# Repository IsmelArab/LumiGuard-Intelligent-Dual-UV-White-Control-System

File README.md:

# LumiGuard-Intelligent-Dual-UV-White-Control-System

# Project Objective:

LumiGuard's goal is to provide a comprehensive solution for applications that require:

Efficient UV disinfection: Using short-wavelength ultraviolet light (275 nm) to eliminate pathogens without risk to operators.

Adjustable white lighting: For real-time process visualization.

Smart security: Proximity detection automatically deactivates UV light if an operator approaches.

Energy efficiency: PWM control of LEDs and low-power mode.

# Key Components and Technologies:

The heart of LumiGuard integrates modern technologies and high-quality components:

ATtiny85 Microcontroller:

The brain of the system manages operating modes, PWM signals, and I2C communication.

VCNL4040 Proximity Sensor:

Detects human presence up to 20 cm away, activating safety protocols.

Specialized LEDs:

UV (275 nm): For disinfection.

White (5630 SMD): For cool, adjustable lighting.

MOSFET Control (DMN3010LSS):

Adjusts light intensity via PWM, minimizing energy losses

Professional PCB Design:

2 layers with a solid ground plane.

Noise filtering, analog/digital separation, and custom silkscreen printing.

Programming Interface (USBasp):

ISP connector for firmware updates.

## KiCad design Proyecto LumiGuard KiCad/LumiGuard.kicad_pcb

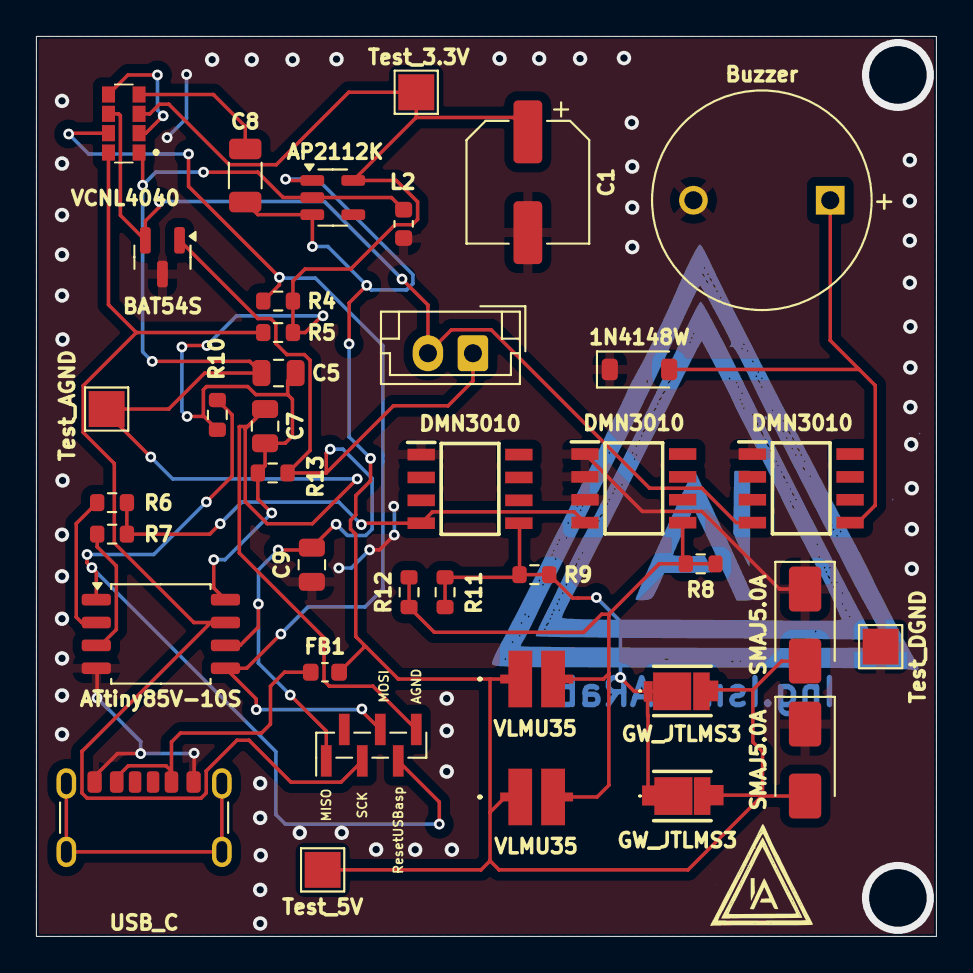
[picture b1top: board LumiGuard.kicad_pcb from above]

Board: 2 copper layers, 50.0 x 50.0 mm, 39 parts (0 on the bottom side), 18 nets.

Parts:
BZ1: Buzzer; MagneticBuzzer_ProSignal_ABI-009-RC
C1: 100uF; CP_Elec_6.3x5.3
C5: 1uF; C_0805_2012Metric
C7, C9: 0.1uF; C_0805_2012Metric
C8: 2.2uF; C_1206_3216Metric
D1: 1N4148W; D_SOD-123
D2: BAT54S; SOT-23
D5, D6: SMAJ5.0A; D_SMA
FB1: 2A; L_0603_1608Metric
IC1: VCNL4040; VCNL4040M3OEH3
J1: Conn_01x02_Pin; JST_EH_B2B-EH-A_1x02_P2.50mm_Vertical
J2: USB_C; USB_C_Receptacle_GCT_USB4125-xx-x-0190_6P_TopMnt_Horizontal
L2: 100uH; L_0603_1608Metric
LED2, LED4: GW_JTLMS3; GWJTLMS3CMG6G9XX5101
LED3, LED6: VLMU35; VLMU35CL20275120
Q1, Q2, Q3: DMN3010; SOIC127P600X175-8N
R4, R5: 2.2k; R_0603_1608Metric
R6, R7, R8, R12: 100; R_0603_1608Metric
R9, R11: 150; R_0603_1608Metric
R10, R13: 10k; R_0603_1608Metric
SPI1: TSW-106-08-F-S; PinHeader_1x06_P1.00mm_Vertical_SMD_Pin1Left
TP1: Test_5V; TestPoint_Pad_2.0x2.0mm
TP2: Test_3.3V; TestPoint_Pad_2.0x2.0mm
TP3: Test_DGND; TestPoint_Pad_2.0x2.0mm
TP4: Test_AGND; TestPoint_Pad_2.0x2.0mm
U1: AP2112K; SOT-23-5
U3: ATtiny85V-10S; SOIC-8_5.3x5.3mm_P1.27mm

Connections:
/Uc: Q1.4 (G), Q2.4 (G), R6.1, R7.1
AGND: C5.1, C7.1, IC1.1 (GND), L2.1, SPI1.6, TP4.1, U1.2 (GND)
Buzzer: BZ1.1 (+), D1.2 (A), Q3.5 (D_1)
DGND: BZ1.2 (-), C1.2, C9.1, D1.1 (K), D2.3 (COM), D5.1 (A1), D6.1 (A1), J2.A12 (GND), J2.B12 (GND), L2.2, Q1.1 (S_1), Q2.1 (S_1), Q2.2 (S_2), Q2.3 (S_3), Q3.1 (S_1), TP3.1, U3.4 (GND)
DLedB: LED2.1 (K_1), LED2.3 (K_2), LED4.1 (K_1), LED4.3 (K_2), Q1.5 (D_1), R9.1, R9.2, R11.1, R11.2
DLedUV: LED3.2 (K_1), LED3.4 (K_2), LED6.2 (K_1), LED6.4 (K_2), Q2.5 (D_1), R8.1, R8.2, R12.1, R12.2
INT/GMofetBuzzer: D2.2 (K), IC1.6 (INT), J1.2, Q3.4 (G)
unnamed: C8.1, IC1.4 (ANODE)
unnamed: IC1.2 (CATHODE_(SENSOR)), IC1.5 (CATHODE_(LED))
PW3.3V: C1.1, C5.2, C7.2, IC1.3 (VDD), R4.2, R5.2, R10.2, R13.2, TP2.1, U1.5 (VOUT), U3.8 (VCC)
PW5V: C8.2, D5.2 (A2), D6.2 (A2), FB1.2, LED2.2 (A_1), LED2.4 (A_2), LED3.1 (A_1), LED3.3 (A_2), LED4.2 (A_1), LED4.4 (A_2), LED6.1 (A_1), LED6.3 (A_2), TP1.1, U1.1 (VIN), U1.3 (EN)
PW5V_1: FB1.1, J2.A9 (VBUS), J2.B9 (VBUS)
Uc(MISO): C9.2, D2.1 (A), J1.1, R13.1, SPI1.1, U3.6 (PB1)
Uc(MOSI (SDAT)): IC1.7 (SDAT), R4.1, SPI1.4, U3.5 (AREF/PB0)
Uc(ResetUSBasp): R10.1, SPI1.5, U3.1 (~RESET/PB5)
Uc(SCK(SCKL)): IC1.8 (SCLK), R5.1, SPI1.3, U3.7 (PB2)
Uc(control led UV): R7.2, U3.3 (XTAL2/PB4)
Uc(control led blancos): R6.2, U3.2 (XTAL1/PB3)

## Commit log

2025-03-29 Create Imagenes
